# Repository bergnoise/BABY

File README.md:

# BABY
 baby-5 sequencer for eurorack

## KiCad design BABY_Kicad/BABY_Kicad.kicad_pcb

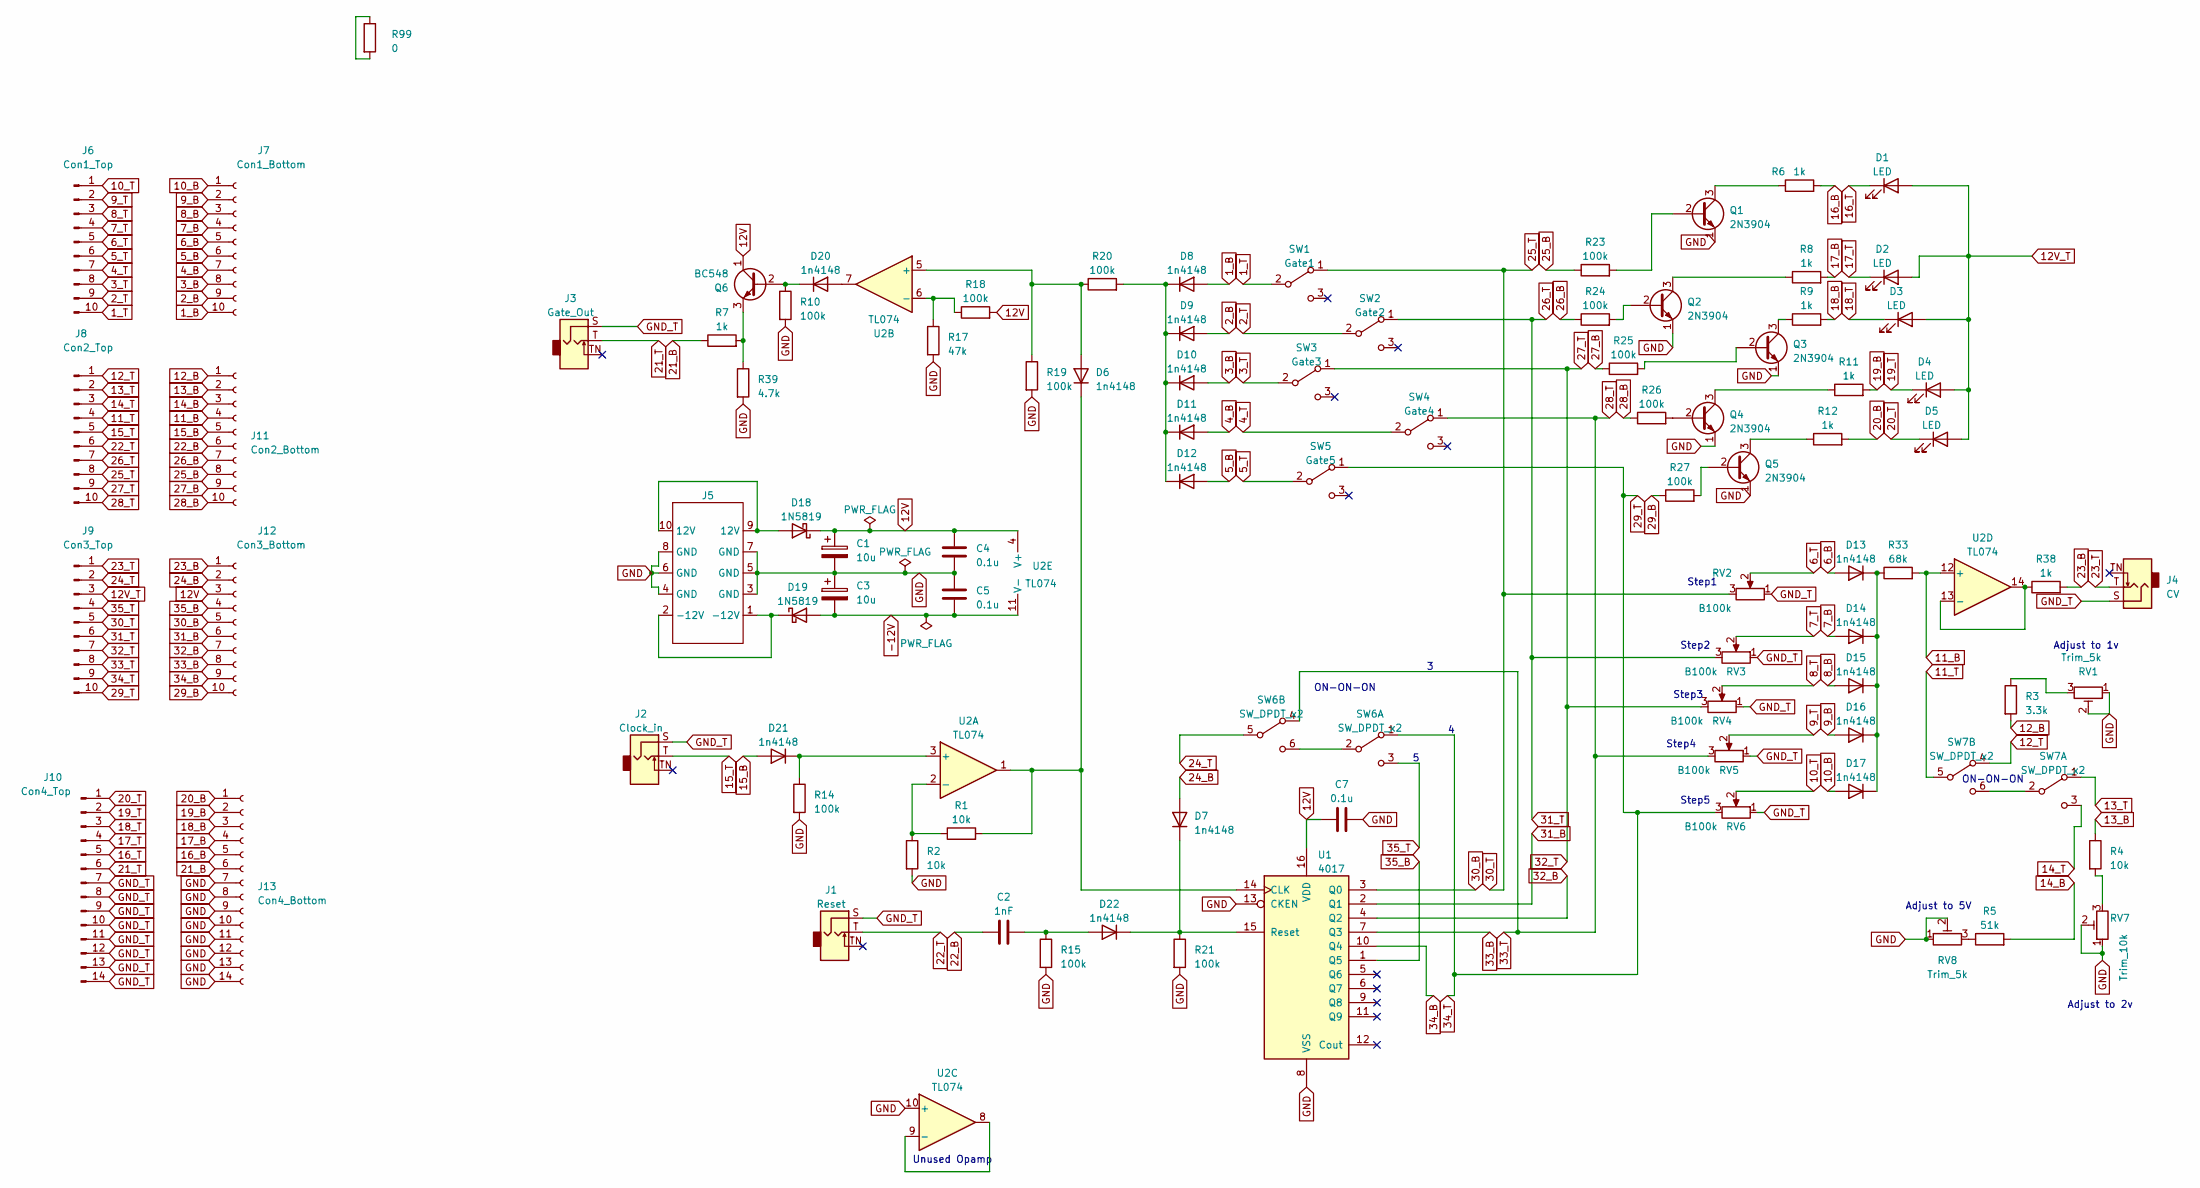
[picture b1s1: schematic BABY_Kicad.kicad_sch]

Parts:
C1, C3: 10u; Capacitor_Radial_D5.0mm_P2.5mm
C2: 1nF; Capacitor_Disc_D3.8mm_W2.6mm_P2.50mm
C4, C5, C7: 0.1u; Capacitor_Disc_D3.8mm_W2.6mm_P2.50mm
D1, D2, D3, D4, D5: LED; LED_D3.0mm
D6, D7, D8, D9, D10, D11, D12, D13, D14, D15, D16, D17, D20, D21, D22: 1n4148; D_DO-35_SOD27_P7.62mm_Horizontal
D18, D19: 1N5819; D_DO-41_SOD81_P10.16mm_Horizontal
J1: Reset; AudioJack_3.5mm
J2: Clock_in; AudioJack_3.5mm
J3: Gate_Out; AudioJack_3.5mm
J4: CV; AudioJack_3.5mm
J5: 10BoxHeaderConnector
J6: Con1_Top; PinHeader_1x10_P2.54mm_Vertical
J7: Con1_Bottom; PinHeader_1x10_P2.54mm_Vertical
J8: Con2_Top; PinHeader_1x10_P2.54mm_Vertical
J9: Con3_Top; PinHeader_1x10_P2.54mm_Vertical
J10: Con4_Top; PinHeader_1x14_P2.54mm_Vertical
J11: Con2_Bottom; PinHeader_1x10_P2.54mm_Vertical
J12: Con3_Bottom; PinHeader_1x10_P2.54mm_Vertical
J13: Con4_Bottom; PinHeader_1x14_P2.54mm_Vertical
Q1, Q2, Q3, Q4, Q5: 2N3904; TO-92_Wide
Q6: BC548; TO-92_Wide
R1, R2, R4: 10k; Resistor_L6.3mm_D2.5mm_P7.62mm_Horizontal
R3: 3.3k; Resistor_L6.3mm_D2.5mm_P7.62mm_Horizontal
R5: 51k; Resistor_L6.3mm_D2.5mm_P7.62mm_Horizontal
R6, R7, R8, R9, R11, R12, R38: 1k; Resistor_L6.3mm_D2.5mm_P7.62mm_Horizontal
R10, R14, R15, R18, R19, R20, R21, R23, R24, R25, R26, R27: 100k; Resistor_L6.3mm_D2.5mm_P7.62mm_Horizontal
R17: 47k; Resistor_L6.3mm_D2.5mm_P7.62mm_Horizontal
R33: 68k; Resistor_L6.3mm_D2.5mm_P7.62mm_Horizontal
R39: 4.7k; Resistor_L6.3mm_D2.5mm_P7.62mm_Horizontal
R99: 0; R_0201_0603Metric
RV1, RV8: Trim_5k; MultiturnTrimmer
RV2, RV3, RV4, RV5, RV6: B100k; Potentiometer_RV09
RV7: Trim_10k; MultiturnTrimmer
SW1: Gate1; SPDT_Tayda
SW2: Gate2; SPDT_Tayda
SW3: Gate3; SPDT_Tayda
SW4: Gate4; SPDT_Tayda
SW5: Gate5; SPDT_Tayda
SW6, SW7: SW_DPDT_x2; DPDT_Tayda
U1: 4017; DIP-16_W7.62mm_Socket_LongPads
U2: TL074; DIP-14_W7.62mm_Socket_LongPads

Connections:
1_B: D8.2 (A), J7.10
1_T: J6.10, SW1.2 (B)
2_B: D9.2 (A), J7.9
2_T: J6.9, SW2.2 (B)
3_B: D10.2 (A), J7.8
3_T: J6.8, SW3.2 (B)
4_B: D11.2 (A), J7.7
4_T: J6.7, SW4.2 (B)
5_B: D12.2 (A), J7.6
5_T: J6.6, SW5.2 (B)
6_B: D13.2 (A), J7.5
6_T: J6.5, RV2.2
7_B: D14.2 (A), J7.4
7_T: J6.4, RV3.2
8_B: D15.2 (A), J7.3
8_T: J6.3, RV4.2
9_B: D16.2 (A), J7.2
9_T: J6.2, RV5.2
10_B: D17.2 (A), J7.1
10_T: J6.1, RV6.2
11_B: J11.4, R33.2, U2.12 (+)
11_T: J8.4, SW7.5 (B)
12V: C1.1, C4.1, C7.1, D18.1 (K), J12.3, Q6.1 (C), R18.2, U1.16 (VDD), U2.4 (V+)
12V_T: D1.2 (A), D2.2 (A), D3.2 (A), D4.2 (A), D5.2 (A), J9.3
12_B: J11.1, R3.2
12_T: J8.1, SW7.4 (A)
13_B: J11.2, R4.1
13_T: J8.2, SW7.1 (A)
14_B: J11.3, R5.2
14_T: J8.3, SW7.3 (C)
15_B: D21.2 (A), J11.5
15_T: J2.T, J8.5
16_B: J13.5, R6.2
16_T: D1.1 (K), J10.5
17_B: J13.4, R8.2
17_T: D2.1 (K), J10.4
18_B: J13.3, R9.2
18_T: D3.1 (K), J10.3
19_B: J13.2, R11.2
19_T: D4.1 (K), J10.2
20_B: J13.1, R12.2
20_T: D5.1 (K), J10.1
21_B: J13.6, R7.1
21_T: J3.T, J10.6
22_B: C2.1, J11.6
22_T: J1.T, J8.6
23_B: J12.1, R38.2
23_T: J4.T, J9.1
24_B: D7.2 (A), J12.2
24_T: J9.2, SW6.5 (B)
25_B: J11.8, R23.1
25_T: J8.8, J9.5, RV2.3, SW1.1 (A)
26_B: J11.7, R24.1
26_T: J8.7, J9.6, RV3.3, SW2.1 (A)
27_B: J11.9, R25.1
27_T: J8.9, J9.7, RV4.3, SW3.1 (A)
28_B: J11.10, R26.1
28_T: J8.10, J9.8, RV5.3, SW4.1 (A), SW6.4 (A)
29_B: J12.10, R27.1
29_T: J9.9, J9.10, RV6.3, SW5.1 (A), SW6.1 (A)
30_B: J12.5, U1.3 (Q0)
31_B: J12.6, U1.2 (Q1)
32_B: J12.7, U1.4 (Q2)
33_B: J12.8, U1.7 (Q3)
34_B: J12.9, U1.10 (Q4)
35_B: J12.4, U1.1 (Q5)
35_T: J9.4, SW6.3 (C)
-12V: C3.2, C5.2, D19.2 (A), U2.11 (V-)
GND: C1.2, C3.1, C4.2, C5.1, C7.2, J5.3 (GND), J5.4 (GND), J5.5 (GND), J5.6 (GND), J5.7 (GND), J5.8 (GND), J13.7, J13.8, J13.9, J13.10, J13.11, J13.12, J13.13, J13.14, Q1.1 (E), Q2.1 (E), Q3.1 (E), Q4.1 (E), Q5.1 (E), R2.2, R10.2, R14.2, R15.2, R17.2, R19.2, R21.2, R39.2, RV1.1, RV1.2, RV7.1, RV7.2, RV8.1, RV8.2, U1.8 (VSS), U1.13 (CKEN), U2.10 (+)
GND_T: J1.S, J2.S, J3.S, J4.S, J10.7, J10.8, J10.9, J10.10, J10.11, J10.12, J10.13, J10.14, RV2.1, RV3.1, RV4.1, RV5.1, RV6.1
unnamed: D6.2 (A), R19.1, R20.1, U2.5 (+)
unnamed: D6.1 (K), R1.2, U1.14 (CLK), U2.1
unnamed: D8.1 (K), D9.1 (K), D10.1 (K), D11.1 (K), D12.1 (K), R20.2
unnamed: D13.1 (K), D14.1 (K), D15.1 (K), D16.1 (K), D17.1 (K), R33.1
unnamed: D18.2 (A), J5.9 (12V), J5.10 (12V)
unnamed: D19.1 (K), J5.1 (-12V), J5.2 (-12V)
unnamed: D20.2 (A), U2.7
unnamed: D20.1 (K), Q6.2 (B), R10.1
unnamed: D21.1 (K), R14.1, U2.3 (+)
unnamed: C2.2, D22.2 (A), R15.1
unnamed: D7.1 (K), D22.1 (K), R21.1, U1.15 (Reset)
unnamed: Q1.2 (B), R23.2
unnamed: Q1.3 (C), R6.1
unnamed: Q2.2 (B), R24.2
unnamed: Q2.3 (C), R8.1
unnamed: Q3.2 (B), R25.2
unnamed: Q3.3 (C), R9.1
unnamed: Q4.2 (B), R26.2
unnamed: Q4.3 (C), R11.1
unnamed: Q5.2 (B), R27.2
unnamed: Q5.3 (C), R12.1
unnamed: Q6.3 (E), R7.2, R39.1
unnamed: R3.1, RV1.3
unnamed: R4.2, RV7.3
unnamed: R5.1, RV8.3
unnamed: R99.1, R99.2
unnamed: SW6.2 (B), SW6.6 (C)
unnamed: SW7.2 (B), SW7.6 (C)
unnamed: R1.1, R2.1, U2.2 (-)
unnamed: R17.1, R18.1, U2.6 (-)
unnamed: U2.8, U2.9 (-)
unnamed: R38.1, U2.13 (-), U2.14

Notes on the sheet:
Unused Opamp
Adjust to 5V
Step5
ON-ON-ON
Adjust to 2v
Step2
Step1
Step3
Adjust to 1v
Step4

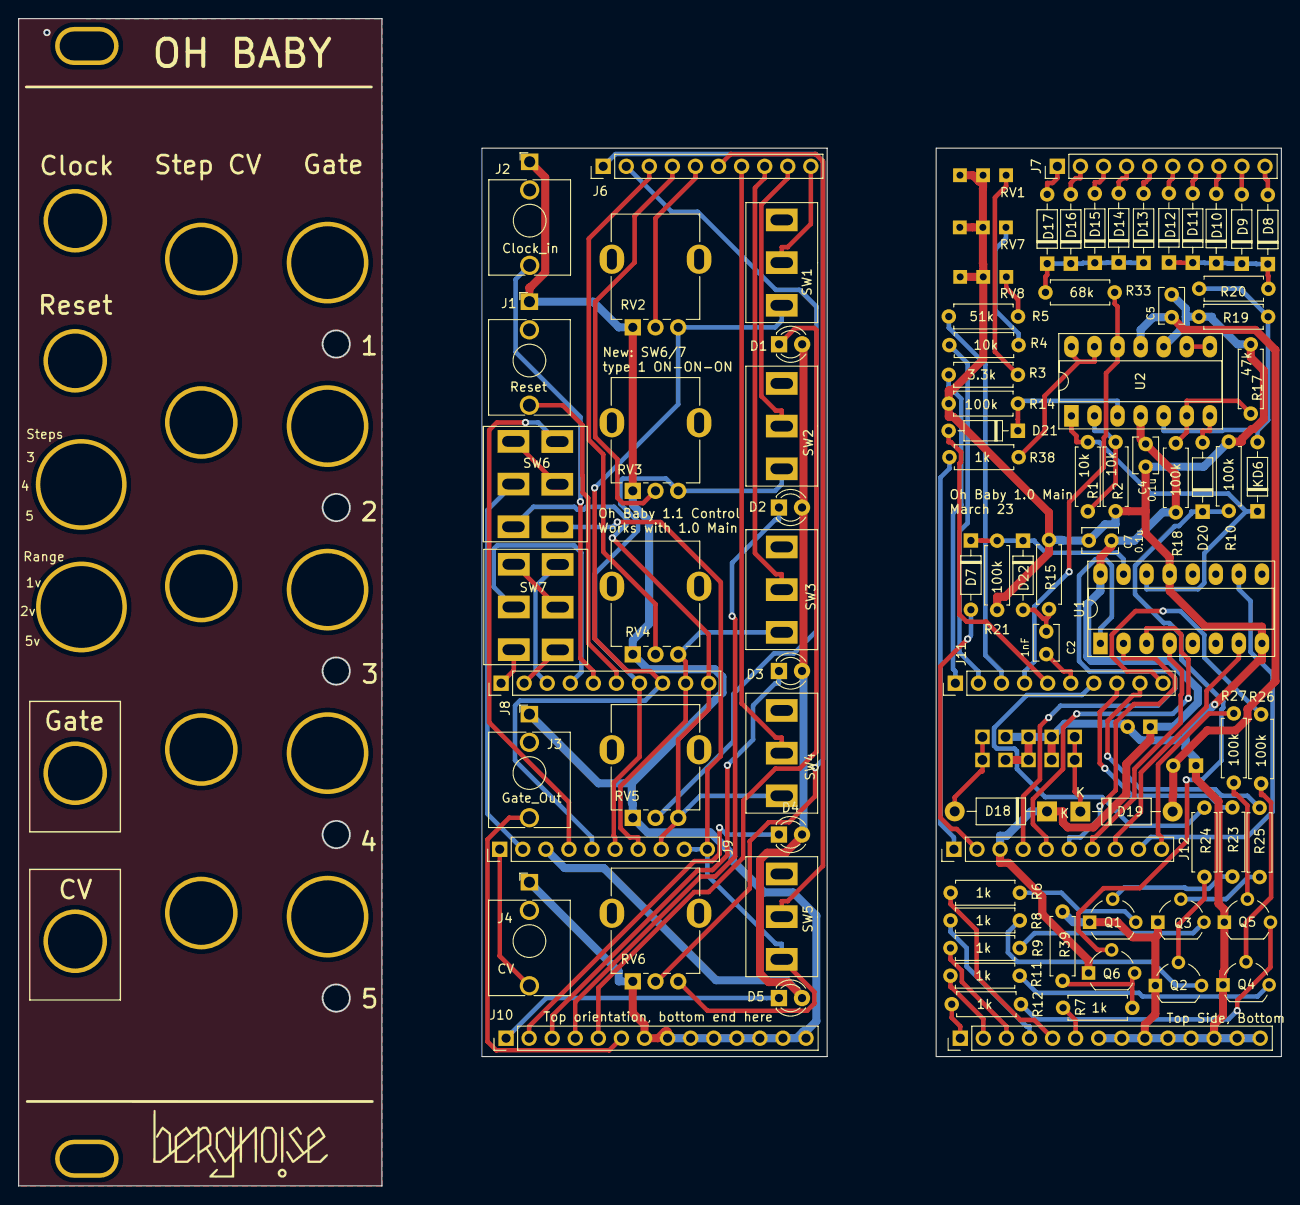
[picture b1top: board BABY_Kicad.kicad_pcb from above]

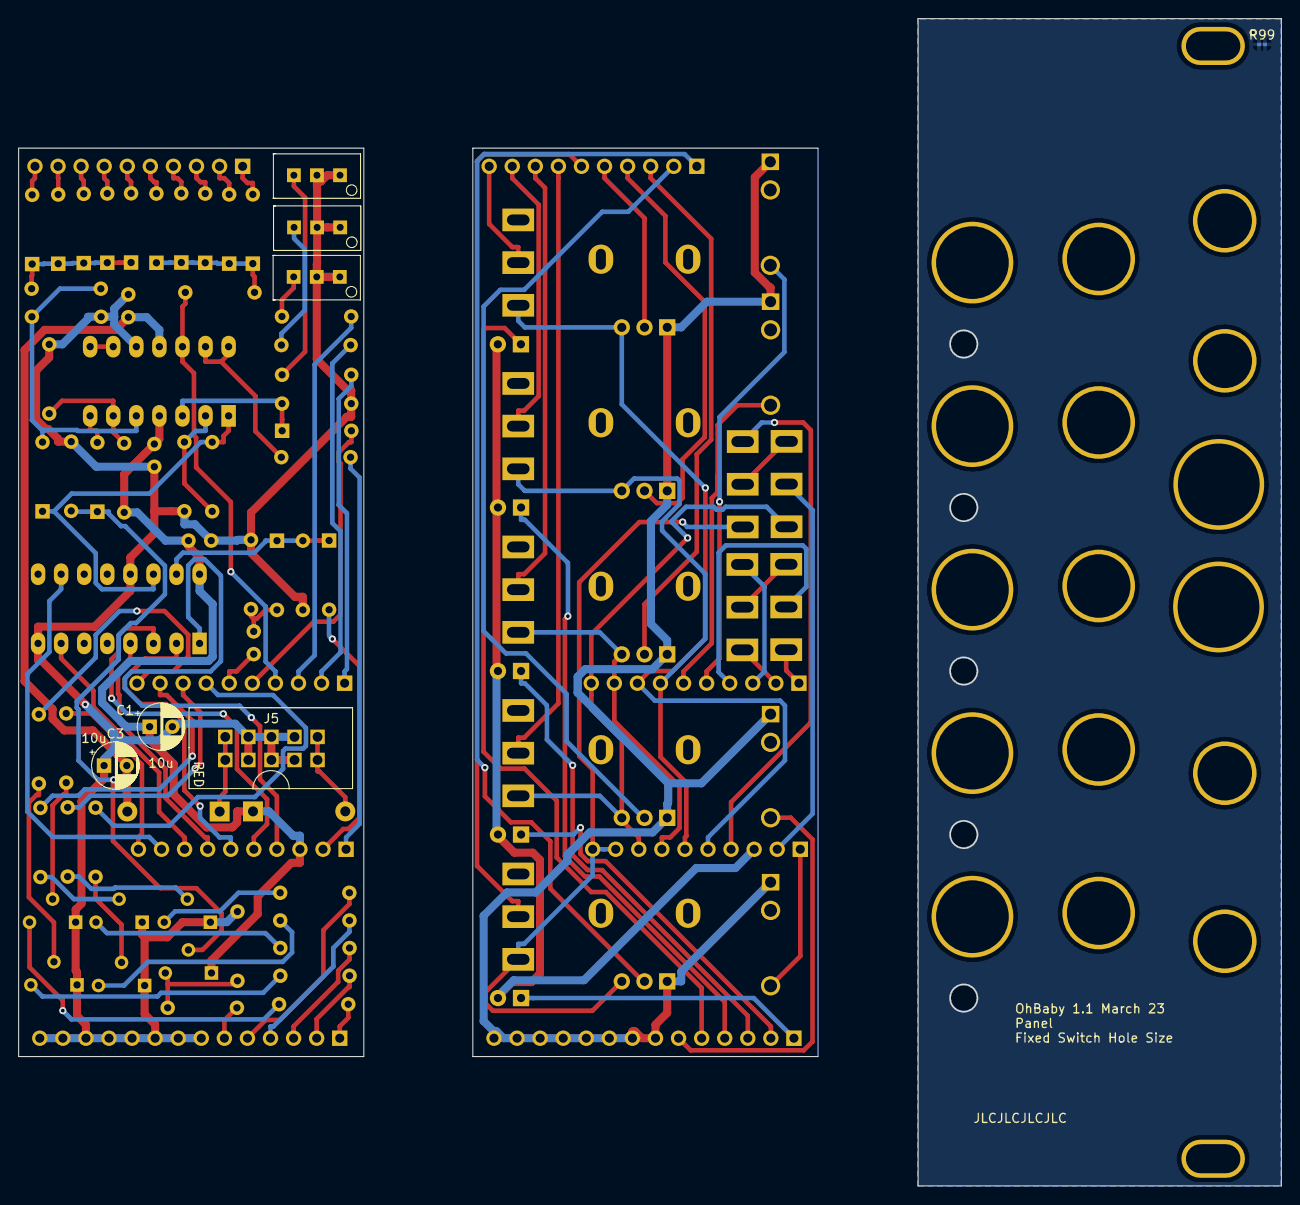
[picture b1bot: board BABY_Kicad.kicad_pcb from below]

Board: 2 copper layers, 138.9 x 128.4 mm, 110 parts (7 on the bottom side), 102 nets.

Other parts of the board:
REF1: Panel_8HP
REF2, REF5, REF12, REF15: PanelHole_AudioJack_3.5mm
REF3, REF7, REF11, REF14, REF17: PanelHole_ToggleSwitch_MTS-101
REF4, REF6, REF10, REF13, REF16: PanelHole_Potentiometer_RV09
REF8, REF9: PanelHole_DPDT_Tayda
Ref**: Val**; logo_v1

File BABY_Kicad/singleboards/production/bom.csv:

Designator,Footprint,Quantity,Value,LCSC Part #
"C1, C3",Capacitor_Radial_D5.0mm_P2.5mm,2,10u,
C2,Capacitor_Disc_D3.8mm_W2.6mm_P2.50mm,1,1nF,
"C4, C5, C7",Capacitor_Disc_D3.8mm_W2.6mm_P2.50mm,3,0.1u,
"D10, D11, D12, D13, D14, D15, D16, D17, D20, D21, D22, D6, D7, D8, D9",D_DO-35_SOD27_P7.62mm_Horizontal,15,1n4148,
"D18, D19",D_DO-41_SOD81_P10.16mm_Horizontal,2,1N5819,
J11,PinHeader_1x10_P2.54mm_Vertical,1,Con2_Bottom,
J12,PinHeader_1x10_P2.54mm_Vertical,1,Con3_Bottom,
J13,PinHeader_1x14_P2.54mm_Vertical,1,Con4_Bottom,
J5,10BoxHeaderConnector,1,~,
J7,PinHeader_1x10_P2.54mm_Vertical,1,Con1_Bottom,
"Q1, Q2, Q3, Q4, Q5",TO-92_Wide,5,2N3904,
Q6,TO-92_Wide,1,BC548,
"R1, R2, R4",Resistor_L6.3mm_D2.5mm_P7.62mm_Horizontal,3,10k,
"R10, R14, R15, R18, R19, R20, R21, R23, R24, R25, R26, R27",Resistor_L6.3mm_D2.5mm_P7.62mm_Horizontal,12,100k,
"R11, R12, R38, R6, R7, R8, R9",Resistor_L6.3mm_D2.5mm_P7.62mm_Horizontal,7,1k,
R17,Resistor_L6.3mm_D2.5mm_P7.62mm_Horizontal,1,47k,
R3,Resistor_L6.3mm_D2.5mm_P7.62mm_Horizontal,1,3.3k,
R33,Resistor_L6.3mm_D2.5mm_P7.62mm_Horizontal,1,68k,
R39,Resistor_L6.3mm_D2.5mm_P7.62mm_Horizontal,1,4.7k,
R5,Resistor_L6.3mm_D2.5mm_P7.62mm_Horizontal,1,51k,
"RV1, RV8",MultiturnTrimmer,2,Trim_5k,
RV7,MultiturnTrimmer,1,Trim_10k,
U1,DIP-16_W7.62mm_Socket_LongPads,1,4017,
U2,DIP-14_W7.62mm_Socket_LongPads,1,TL074,

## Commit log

2023-03-13 finished schematic
2023-03-14 started pcb
2023-03-15 finished pcb
2023-03-26 first testrun
2023-07-04 Fixes
